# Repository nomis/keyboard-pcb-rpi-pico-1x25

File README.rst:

Keyboard PCB for Raspberry Pi Pico (25x1)
=========================================

Overview
--------

PCB for a 25x1 keyboard connected to a Raspberry Pi Pico.

.. image:: keyboard-pcb-rpi-pico-25x1.svg
   :alt: Front and back of PCB

Dimensions: 25.4mm W × 499.11mm H × ~32mm D

Usage
-----

This is a KiCad project. Manufacture the PCB and then insert a Raspberry Pi
Pico at the top with the USB connector facing upwards. Fit Cherry MX switches
in all positions and connect external RGB LEDs (optional).

Components
----------

+-----------+----------------------------------------------------------------+
| Ref       | Name                                                           |
+===========+================================================================+
|           | Raspberry Pi Pico                                              |
+-----------+----------------------------------------------------------------+
| PICO-L1   | 1x20 Pin Socket, Through Hole (2.54mm)                         |
+-----------+----------------------------------------------------------------+
| PICO-R1   | 1x20 Pin Socket, Through Hole (2.54mm)                         |
+-----------+----------------------------------------------------------------+
| LEDS1     | 1x04 Pin Header, Right-Angled Through Hole (2.54mm) (optional) |
+-----------+----------------------------------------------------------------+
| SW1..SW25 | Cherry MX keyswitch (1.00u)                                    |
+-----------+----------------------------------------------------------------+

Switches
--------

1. GP0
2. GP1
3. GP2
4. GP11
5. GP10

6. GP9
7. GP8
8. GP7
9. GP6
10. GP5

11. GP4
12. GP3
13. GP15
14. GP14
15. GP13

16. GP12
17. GP19
18. GP18
19. GP17
20. GP16

21. GP20
22. GP21
23. GP22
24. GP26
25. GP27

LEDs
----

The LEDS1 pin header has GP28 for data, 3.3V, 5V and GND.

Related Software
----------------

* `QMK (Quantum Mechanical Keyboard) Firmware <https://github.com/nomis/qmk_firmware/tree/rpi_pico_25x1/keyboards/nomis/rpi_pico_25x1>`_

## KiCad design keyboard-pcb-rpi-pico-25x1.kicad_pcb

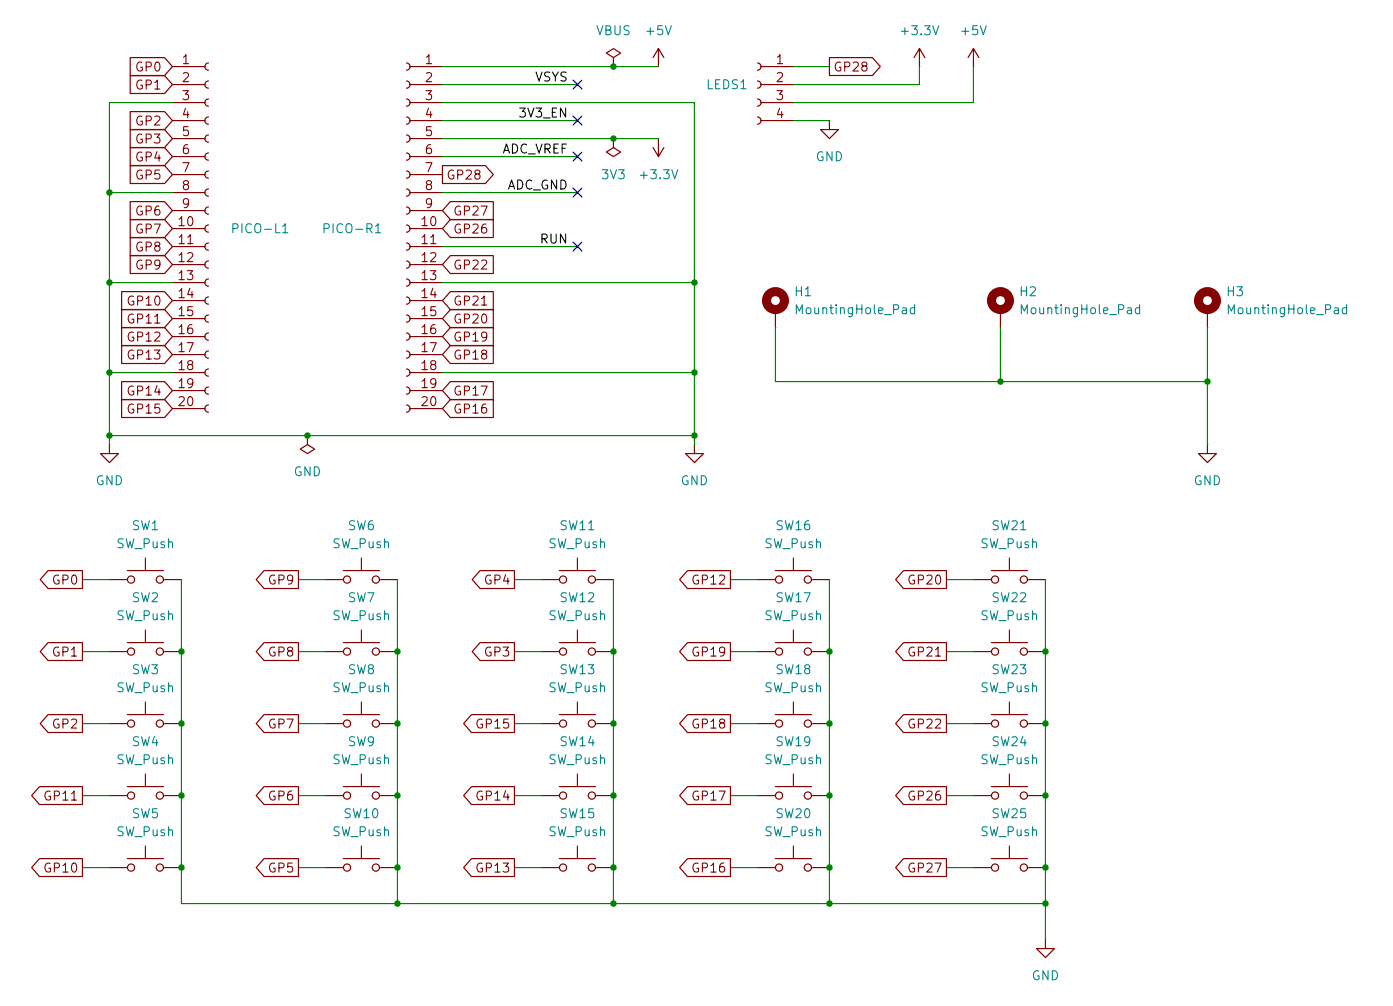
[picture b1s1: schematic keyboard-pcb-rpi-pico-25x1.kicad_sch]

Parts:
H1, H2, H3: MountingHole_Pad; MountingHole_3.2mm_M3_Pad
LEDS1: Conn_01x04_Socket; PinHeader_1x04_P2.54mm_Horizontal
PICO-L1: Conn_01x20_Socket; PinSocket_1x20_P2.54mm_Vertical
PICO-R1: Conn_01x20_Socket; PinSocket_1x20_P2.54mm_Vertical
SW1, SW2, SW3, SW4, SW5, SW6, SW7, SW8, SW9, SW10, SW11, SW12, SW13, SW14, SW15, SW16, SW17, SW18, SW19, SW20, SW21, SW22, SW23, SW24, SW25: SW_Push; SW_Cherry_MX_1.00u_PCB

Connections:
+3.3V: LEDS1.2, PICO-R1.5
+5V: LEDS1.3, PICO-R1.1
/3V3_EN: PICO-R1.4
/ADC_GND: PICO-R1.8
/ADC_VREF: PICO-R1.6
/RUN: PICO-R1.11
/VSYS: PICO-R1.2
GND: H1.1, H2.1, H3.1, LEDS1.4, PICO-L1.3, PICO-L1.8, PICO-L1.13, PICO-L1.18, PICO-R1.3, PICO-R1.13, PICO-R1.18, SW1.2, SW2.2, SW3.2, SW4.2, SW5.2, SW6.2, SW7.2, SW8.2, SW9.2, SW10.2, SW11.2, SW12.2, SW13.2, SW14.2, SW15.2, SW16.2, SW17.2, SW18.2, SW19.2, SW20.2, SW21.2, SW22.2, SW23.2, SW24.2, SW25.2
GP0: PICO-L1.1, SW1.1
GP1: PICO-L1.2, SW2.1
GP2: PICO-L1.4, SW3.1
GP3: PICO-L1.5, SW12.1
GP4: PICO-L1.6, SW11.1
GP5: PICO-L1.7, SW10.1
GP6: PICO-L1.9, SW9.1
GP7: PICO-L1.10, SW8.1
GP8: PICO-L1.11, SW7.1
GP9: PICO-L1.12, SW6.1
GP10: PICO-L1.14, SW5.1
GP11: PICO-L1.15, SW4.1
GP12: PICO-L1.16, SW16.1
GP13: PICO-L1.17, SW15.1
GP14: PICO-L1.19, SW14.1
GP15: PICO-L1.20, SW13.1
GP16: PICO-R1.20, SW20.1
GP17: PICO-R1.19, SW19.1
GP18: PICO-R1.17, SW18.1
GP19: PICO-R1.16, SW17.1
GP20: PICO-R1.15, SW21.1
GP21: PICO-R1.14, SW22.1
GP22: PICO-R1.12, SW23.1
GP26: PICO-R1.10, SW24.1
GP27: PICO-R1.9, SW25.1
GP28: LEDS1.1, PICO-R1.7

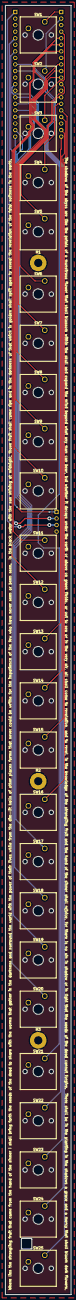
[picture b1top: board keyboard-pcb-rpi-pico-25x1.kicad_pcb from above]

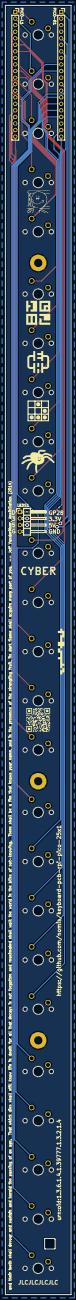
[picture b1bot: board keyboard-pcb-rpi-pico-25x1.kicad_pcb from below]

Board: 2 copper layers, 25.4 x 499.1 mm, 38 parts (10 on the bottom side), 29 nets.

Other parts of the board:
CYBER: LOGO
EHLAB: LOGO
FEZ1, FEZ2: LOGO
MrMeeseeks: LOGO
QRCODE: LOGO
Spider: LOGO

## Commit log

2025-06-05 Add text
2025-06-05 Add mounting holes and art
2025-06-05 Move top mounting hole further up
2025-06-05 Make Mr Meeseeks thicker
2025-06-05 Add README
2025-06-05 Add glider
2025-06-05 Add spider
2025-06-05 Add CYBER
2025-06-05 Remove extra newlines
2025-06-05 Add QR code
2025-06-05 Add extra alignment hole
2025-06-05 Use rounded corners for hole
2025-06-05 Improve FEZ2 puzzle
2025-06-05 Cleanup tracks
2025-06-05 Configure gerber output
2025-06-05 Add Gerber files for JLCPCB
2025-06-05 Fix width of Pico pin headers
2025-06-05 Update Gerber files for JLCPCB
2025-06-05 Increase thickness of power traces
2025-06-05 Ignore zip files
2025-06-07 Add Area X quote
2025-06-07 Render the PCB as an image
2025-06-07 Add dimensions to readme
2025-06-07 Add rendered PCB to the readme
2025-06-08 Document the GPIOs
2025-06-08 Change routing to improve ground planes
2025-06-08 Move vias so that they're not directly under silkscreen
2025-06-08 Simplify Makefile
2025-06-08 Remove title from SVGs
2025-06-09 Fix keyboard/project name
2025-06-09 Update QR code URL
2025-06-10 Add components list
2025-06-12 Add keyswitch to component list
2025-06-13 Add QMK link
2025-06-15 Move the ground to the other side of the switch pins
2025-06-15 Fix schematic power error messages by adding PWR_FLAG
2025-06-15 Update dimensions when key switches are added
2025-06-21 Add laser cutter patterns
2025-06-25 Fix PCB image
2025-06-28 Fix kibot command
